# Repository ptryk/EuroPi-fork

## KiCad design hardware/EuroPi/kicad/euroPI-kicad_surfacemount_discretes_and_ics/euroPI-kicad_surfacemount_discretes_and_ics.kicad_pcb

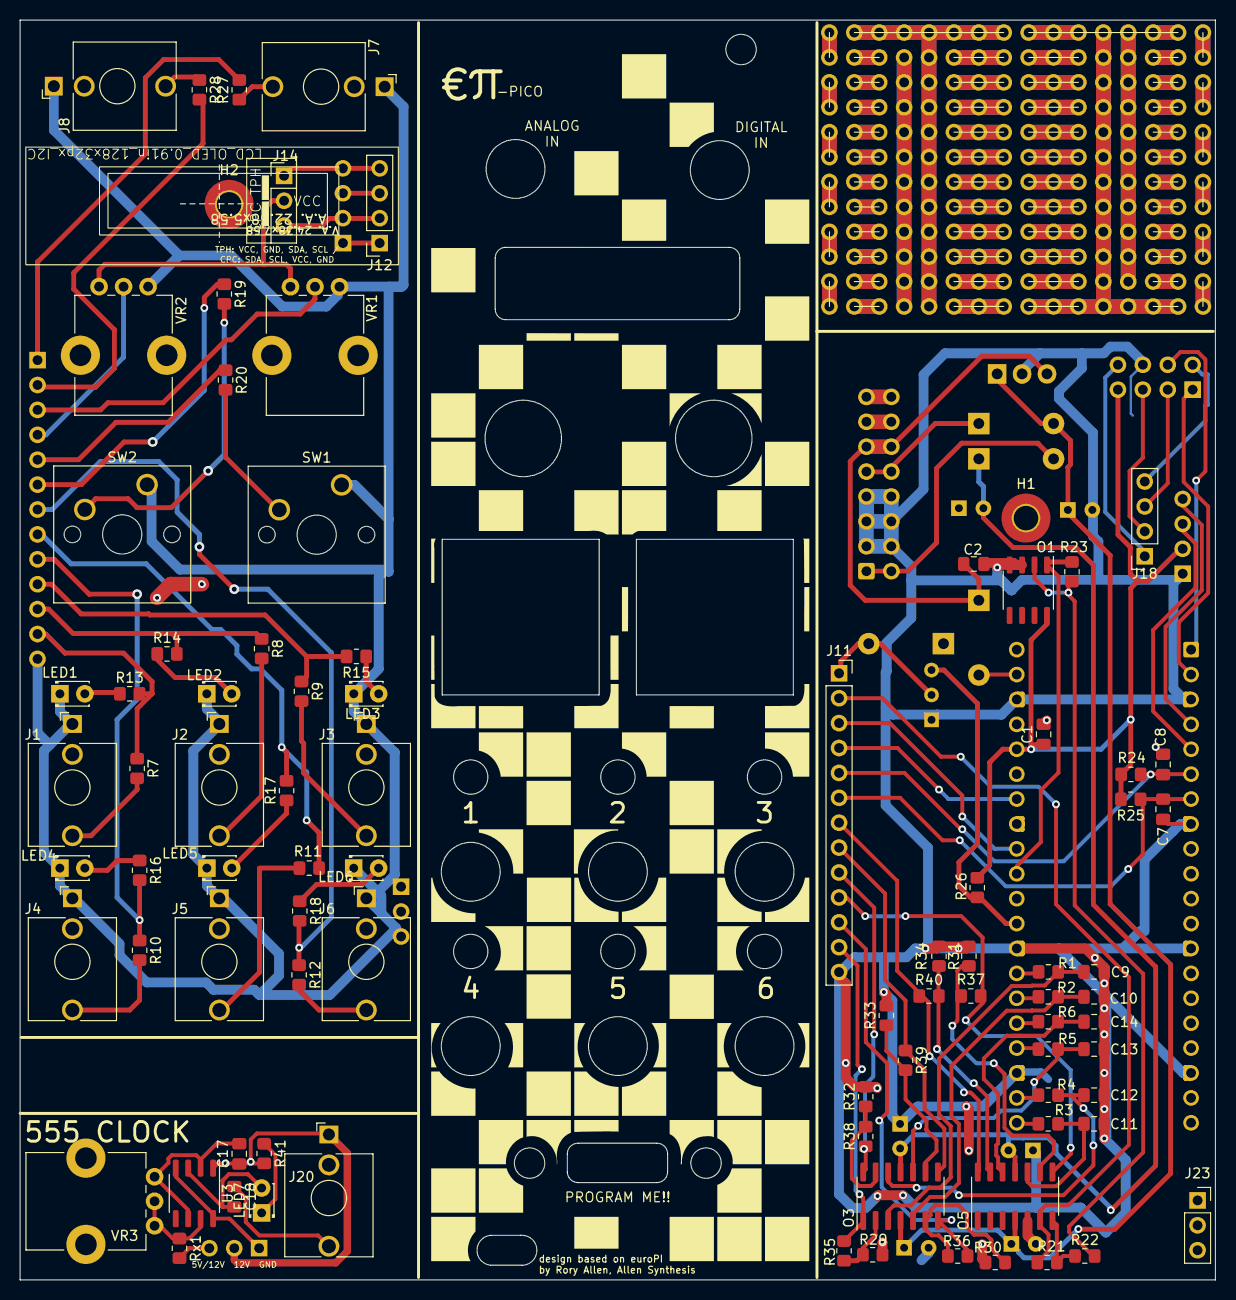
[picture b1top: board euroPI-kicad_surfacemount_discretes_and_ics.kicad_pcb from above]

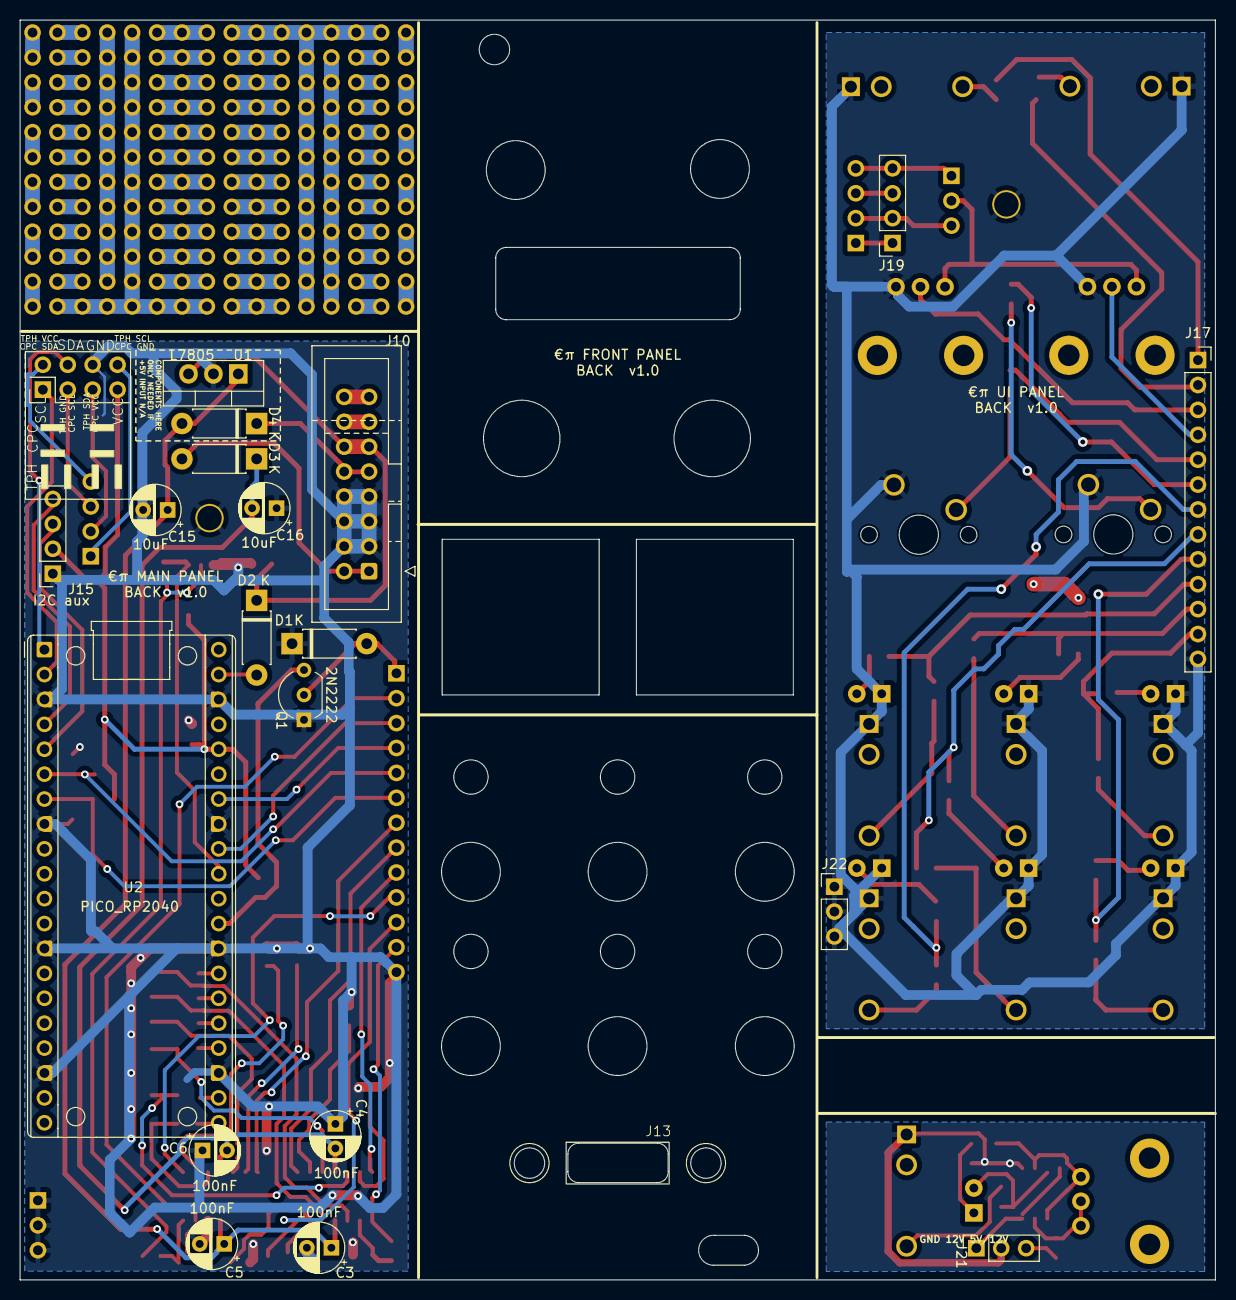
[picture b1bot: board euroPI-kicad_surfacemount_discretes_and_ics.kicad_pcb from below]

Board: 2 copper layers, 121.9 x 128.5 mm, 107 parts (21 on the bottom side), 73 nets.

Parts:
C1, C2, C17: 1uF; C_0805_2012Metric_Pad1.18x1.45mm_HandSolder
C3, C4, C5, C6: 100nF; CP_Radial_D5.0mm_P2.50mm
C7, C8, C9, C10, C11, C12, C13, C14: 100nF; C_0805_2012Metric_Pad1.18x1.45mm_HandSolder
C15, C16: 10uF; CP_Radial_D5.0mm_P2.50mm
C18: 10uF; C_0805_2012Metric_Pad1.18x1.45mm_HandSolder
D1, D2, D3, D4: 1N5817 Schottky Diode; D_DO-41_SOD81_P7.62mm_Horizontal
H1, H2: MountingHole_Pad; MountingHole_2.5mm_Pad_TopOnly
J1: Output 1 Jack; Jack_3.5mm_QingPu_WQP-PJ398SM_Vertical_CircularHoles
J2: Output 2 Jack; Jack_3.5mm_QingPu_WQP-PJ398SM_Vertical_CircularHoles
J3: Output 3 Jack; Jack_3.5mm_QingPu_WQP-PJ398SM_Vertical_CircularHoles
J4: Output 4 Jack; Jack_3.5mm_QingPu_WQP-PJ398SM_Vertical_CircularHoles
J5, J20: Output 5 Jack; Jack_3.5mm_QingPu_WQP-PJ398SM_Vertical_CircularHoles
J6: Output 6 Jack; Jack_3.5mm_QingPu_WQP-PJ398SM_Vertical_CircularHoles
J7: Digital Input Jack; Jack_3.5mm_QingPu_WQP-PJ398SM_Vertical_CircularHoles
J8: Analogue Input Jack; Jack_3.5mm_QingPu_WQP-PJ398SM_Vertical_CircularHoles
J10: Eurorack Power 2x8 16p; IDC-Header_euroRack-2x08_and_2x05_P2.54mm_Vertical
J11: Conn_01x13_Socket; PinSocket_1x13_P2.54mm_Vertical
J12: OLED 64x128; LCD_OLED_0.91in_128x32px_I2C
J13: USB_B_Micro; USBmicroB_panelMount
J14: Conn_01x03_Pin; OLED_switch_TPH-CPC_VCC+3v
J15: I2C aux; PinSocket_1x04_P2.54mm_Vertical
J16: Conn_02x04_Top_Bottom; OLED_switch_TPH-CPC
J17: Conn_01x13_Pin; PinSocket_1x13_P2.54mm_Vertical
J18: Conn_01x04_Pin; PinSocket_1x04_P2.54mm_Vertical
J19: Conn_01x04_Socket; PinSocket_1x04_P2.54mm_Vertical
J21: Conn_01x03_Pin; PinSocket_1x03_P2.54mm_Vertical
J22: Conn_01x03_Pin; PinHeader_1x03_P2.54mm_Vertical
J23: Conn_01x03_Socket; PinSocket_1x03_P2.54mm_Vertical
LED1, LED2, LED3, LED4, LED5, LED6, LED7: LED; LED_D1.8mm_W3.3mm_H2.4mm
O1: MCP6002; SO-8_3.9x4.9mm_P1.27mm
O3: TL074-1; SO-14_3.9x8.65mm_P1.27mm
O5: TL074-2; SO-14_3.9x8.65mm_P1.27mm
Q1: 2N2222; TO-92_Inline_Wide
R1, R2, R3, R4, R5, R6, R7, R8, R9, R10, R11, R12, R19, R20, R41: 1K; R_0805_2012Metric_Pad1.20x1.40mm_HandSolder
R13, R14, R15, R16, R17, R18: 4K7; R_0805_2012Metric_Pad1.20x1.40mm_HandSolder
R21, R22, R23: 22K; R_0805_2012Metric_Pad1.20x1.40mm_HandSolder
R24, R25, R26: 10K; R_0805_2012Metric_Pad1.20x1.40mm_HandSolder
R27, R28, R29, R30, R31, R32, R33, R34: 100K; R_0805_2012Metric_Pad1.20x1.40mm_HandSolder
R35, R36, R37, R38, R39, R40: 220K; R_0805_2012Metric_Pad1.20x1.40mm_HandSolder
Rx1: 1K; R_0805_2012Metric_Pad1.20x1.40mm_HandSolder
SW1, SW2: SW_Push; SW_Cherry_MX_1.00u_PCB
U1: L7805; TO-220-3_Vertical
U2: PICO_RP2040; RaspberryPi_Pico_Common_THT-minimal_courtyard_assumed_mount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
U3: LM555xN; SO-8_3.9x4.9mm_P1.27mm
VR1: KNOB 1; Potentiometer_Bourns_PTV09A-1_Single_Vertical
VR2: KNOB 2; Potentiometer_Bourns_PTV09A-1_Single_Vertical
VR3: 10K; Potentiometer_Bourns_PTV09A-1_Single_Vertical

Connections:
+5V: C2.1, D2.1 (A), J10.11, J10.12, J21.3, Rx1.2, U1.3 (OUT)
-12V: C4.2, C6.2, C16.2, D3.1 (A), O3.11 (V-), O5.11 (V-)
CJ1: J11.12, J17.12, O3.1, R7.1, R13.2, R35.1
CJ2: J11.11, J17.11, O3.7, R8.1, R14.2, R36.1
CJ3: J11.10, J17.10, O5.8, R9.1, R15.2, R37.1
CJ4: J11.9, J17.9, O3.14, R10.1, R16.2, R38.1
CJ5: J11.8, J17.8, O3.8, R11.1, R17.2, R39.1
CJ6: J11.7, J17.7, O5.14, R12.1, R18.2, R40.1
CJA: J11.2, J17.2, O5.6 (-), R21.1, R28.2
CJD: D1.2 (K), J11.1, J17.1, Q1.2 (B), R27.2
CK1: J11.3, J17.3, U2.32 (GP27), VR1.2
CK2: J11.4, J17.4, U2.34 (GP28), VR2.2
CS1: C8.1, J11.5, J17.5, R20.1, R24.1, U2.6 (GP4)
CS2: C7.1, J11.6, J17.6, R19.1, R25.1, U2.7 (GP5)
GP0: J16.6, U2.1 (GP0)
GP1: J16.1, U2.2 (GP1)
GP2: J15.4, U2.4 (GP2)
GP3: J15.3, U2.5 (GP3)
GP16: R3.2, U2.21 (GP16)
GP17: R4.2, U2.22 (GP17)
GP18: R5.2, U2.24 (GP18)
GP19: R6.2, U2.25 (GP19)
GP20: R2.2, U2.26 (GP20)
GP21: R1.2, U2.27 (GP21)
GP22: Q1.3 (C), R26.2, U2.29 (GP22)
GP26: O1.1, R23.2, U2.31 (GP26)
I2C_GND: C1.2, C2.2, C3.2, C4.1, C5.2, C6.1, C7.2, C8.2, C9.2, C10.2, C11.2, C12.2, C13.2, C14.2, C15.2, C16.1, C17.1, D1.1 (A), H1.1, H2.1, J1.S, J2.S, J3.S, J4.S, J5.S, J6.S, J7.S, J8.S, J10.3, J10.4, J10.5, J10.6, J10.7, J10.8, J11.13, J15.1, J16.7, J17.13, J20.S, J21.2, J22.1, J22.2, J22.3, J23.1, J23.2, J23.3, LED1.1 (K), LED2.1 (K), LED3.1 (K), LED4.1 (K), LED5.1 (K), LED6.1 (K), O1.3 (+), O1.4 (V-), O5.5 (+), Q1.1 (E), R29.2, R30.2, R31.2, R32.2, R33.2, R34.2, R41.2, SW1.1, SW2.1, U1.2 (GND), U2.3 (GND), U2.8 (GND), U2.13 (GND), U2.18 (GND), U2.23 (GND), U2.28 (GND), U2.33 (GND), U2.38 (GND), U3.1 (GND), VR1.3, VR2.3
I2C_VCC: C1.1, J14.2, J15.2, J16.4, O1.8 (V+), R24.2, R25.2, R26.1, U2.36 (3V3), VR1.1, VR2.1
unnamed: C18.1, J20.T
unnamed: D2.2 (K), U2.39 (VSYS)
unnamed: D3.2 (K), J10.1, J10.2
unnamed: D4.1 (A), J10.9, J10.10
unnamed: J1.T, R7.2
unnamed: J2.T, R8.2
unnamed: J3.T, R9.2
unnamed: J4.T, R10.2
unnamed: J5.T, R11.2
unnamed: J6.T, R12.2
unnamed: J7.T, R27.1
unnamed: J8.T, R28.1
unnamed: J10.13, J10.14
unnamed: J10.15, J10.16
unnamed: LED1.2 (A), R13.1
unnamed: LED2.2 (A), R14.1
unnamed: LED3.2 (A), R15.1
unnamed: LED4.2 (A), R16.1
unnamed: LED5.2 (A), R17.1
unnamed: LED6.2 (A), R18.1
unnamed: C18.2, LED7.2 (A), U3.3 (Q)
unnamed: LED7.1 (K), R41.1
unnamed: O1.2 (-), R22.2, R23.1
unnamed: C9.1, O3.3 (+), R1.1
unnamed: O3.2 (-), R29.1, R35.2
unnamed: C10.1, O3.5 (+), R2.1
unnamed: O3.6 (-), R30.1, R36.2
unnamed: C13.1, O3.10 (+), R5.1
unnamed: O3.9 (-), R33.1, R39.2
unnamed: C12.1, O3.12 (+), R4.1
unnamed: O3.13 (-), R32.1, R38.2
unnamed: O5.7, R21.2, R22.1
unnamed: C11.1, O5.10 (+), R3.1
unnamed: O5.9 (-), R31.1, R37.2
unnamed: C14.1, O5.12 (+), R6.1
unnamed: O5.13 (-), R34.1, R40.2
unnamed: R19.2, SW2.2
unnamed: R20.2, SW1.2
unnamed: Rx1.1, U3.7 (DIS), VR3.2, VR3.3
unnamed: C17.2, U3.2 (TR), U3.6 (THR), VR3.1
TPH GND / CPC SCL: J12.3, J16.2, J18.3, J19.3
TPH SCL / CPC GND: J12.1, J16.8, J18.1, J19.1
TPH SDA / CPC VCC: J12.2, J14.3, J16.3, J18.2, J19.2
TPH VCC / CPC SDA: J12.4, J14.1, J16.5, J18.4, J19.4
~: C3.1, C5.1, C15.1, D4.2 (K), J21.1, O3.4 (V+), O5.4 (V+), U1.1 (IN), U3.4 (R), U3.8 (VCC)

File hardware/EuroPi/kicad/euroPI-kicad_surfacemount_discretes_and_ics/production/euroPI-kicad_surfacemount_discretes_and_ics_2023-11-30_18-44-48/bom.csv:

Designator,Footprint,Quantity,Value,LCSC Part #
"C1, C17, C2",0805,3,1uF,
"C10, C11, C12, C13, C14, C3, C4, C5, C6, C7, C8, C9",0805,12,100nF,
"C15, C16, C18",0805,3,10uF,
"D1, D2, D3, D4",0805,4,"type=""D"" model=""DIODE"" lib=""""",
J1,Jack_3.5mm_QingPu_WQP-PJ398SM_Vertical_CircularHoles,1,Output 1 Jack,
J10,IDC-Header_euroRack-2x08_and_2x05_P2.54mm_Vertical,1,Eurorack Power 2x8 16p,
J11,PinSocket_1x13_P2.54mm_Vertical,1,Conn_01x13_Socket,
J12,LCD_OLED_0.91in_128x32px_I2C,1,OLED 64x128,
J13,USBmicroB_panelMount,1,USB_B_Micro,
J14,OLED_switch_TPH-CPC_VCC+3v,1,Conn_01x03_Pin,
"J15, J18",PinSocket_1x04_P2.54mm_Vertical,2,Conn_01x04_Pin,
J16,OLED_switch_TPH-CPC,1,Conn_02x04_Top_Bottom,
J17,PinSocket_1x13_P2.54mm_Vertical,1,Conn_01x13_Pin,
J19,PinSocket_1x04_P2.54mm_Vertical,1,Conn_01x04_Socket,
J2,Jack_3.5mm_QingPu_WQP-PJ398SM_Vertical_CircularHoles,1,Output 2 Jack,
"J20, J5",Jack_3.5mm_QingPu_WQP-PJ398SM_Vertical_CircularHoles,2,Output 5 Jack,
J21,PinSocket_1x03_P2.54mm_Vertical,1,Conn_01x03_Pin,
J3,Jack_3.5mm_QingPu_WQP-PJ398SM_Vertical_CircularHoles,1,Output 3 Jack,
J4,Jack_3.5mm_QingPu_WQP-PJ398SM_Vertical_CircularHoles,1,Output 4 Jack,
J6,Jack_3.5mm_QingPu_WQP-PJ398SM_Vertical_CircularHoles,1,Output 6 Jack,
J7,Jack_3.5mm_QingPu_WQP-PJ398SM_Vertical_CircularHoles,1,Digital Input Jack,
J8,Jack_3.5mm_QingPu_WQP-PJ398SM_Vertical_CircularHoles,1,Analogue Input Jack,
"LED1, LED2, LED3, LED4, LED5, LED6, LED7",LED_D1.8mm_W3.3mm_H2.4mm,7,LED,
O1,SO-8_3.9x4.9mm_P1.27mm,1,MCP6002,
O3,SO-14_3.9x8.65mm_P1.27mm,1,TL074-1,
O5,SO-14_3.9x8.65mm_P1.27mm,1,TL074-2,
Q1,SOT-23,1,2N2222,
"R1, R10, R11, R12, R19, R2, R20, R3, R4, R41, R5, R6, R7, R8, R9, Rx1",0805,16,1K,
"R13, R14, R15, R16, R17, R18",0805,6,4K7,
"R21, R22, R23",0805,3,22K,
"R24, R25, R26",0805,3,10K,
"R27, R28, R29, R30, R31, R32, R33, R34",0805,8,100K,
"R35, R36, R37, R38, R39, R40",0805,6,220K,
"SW1, SW2",SW_Cherry_MX_1.00u_PCB,2,SW_Push,
U1,TO-252-3_TabPin2,1,L7805,
U2,RaspberryPi_Pico_Common_THT-minimal_courtyard_assumed_mounted_high,1,PICO_RP2040,
U3,SO-8_3.9x4.9mm_P1.27mm,1,LM555xN,
VR1,Potentiometer_Bourns_PTV09A-1_Single_Vertical,1,KNOB 1,
VR2,Potentiometer_Bourns_PTV09A-1_Single_Vertical,1,KNOB 2,
VR3,Potentiometer_Bourns_PTV09A-1_Single_Vertical,1,10K,

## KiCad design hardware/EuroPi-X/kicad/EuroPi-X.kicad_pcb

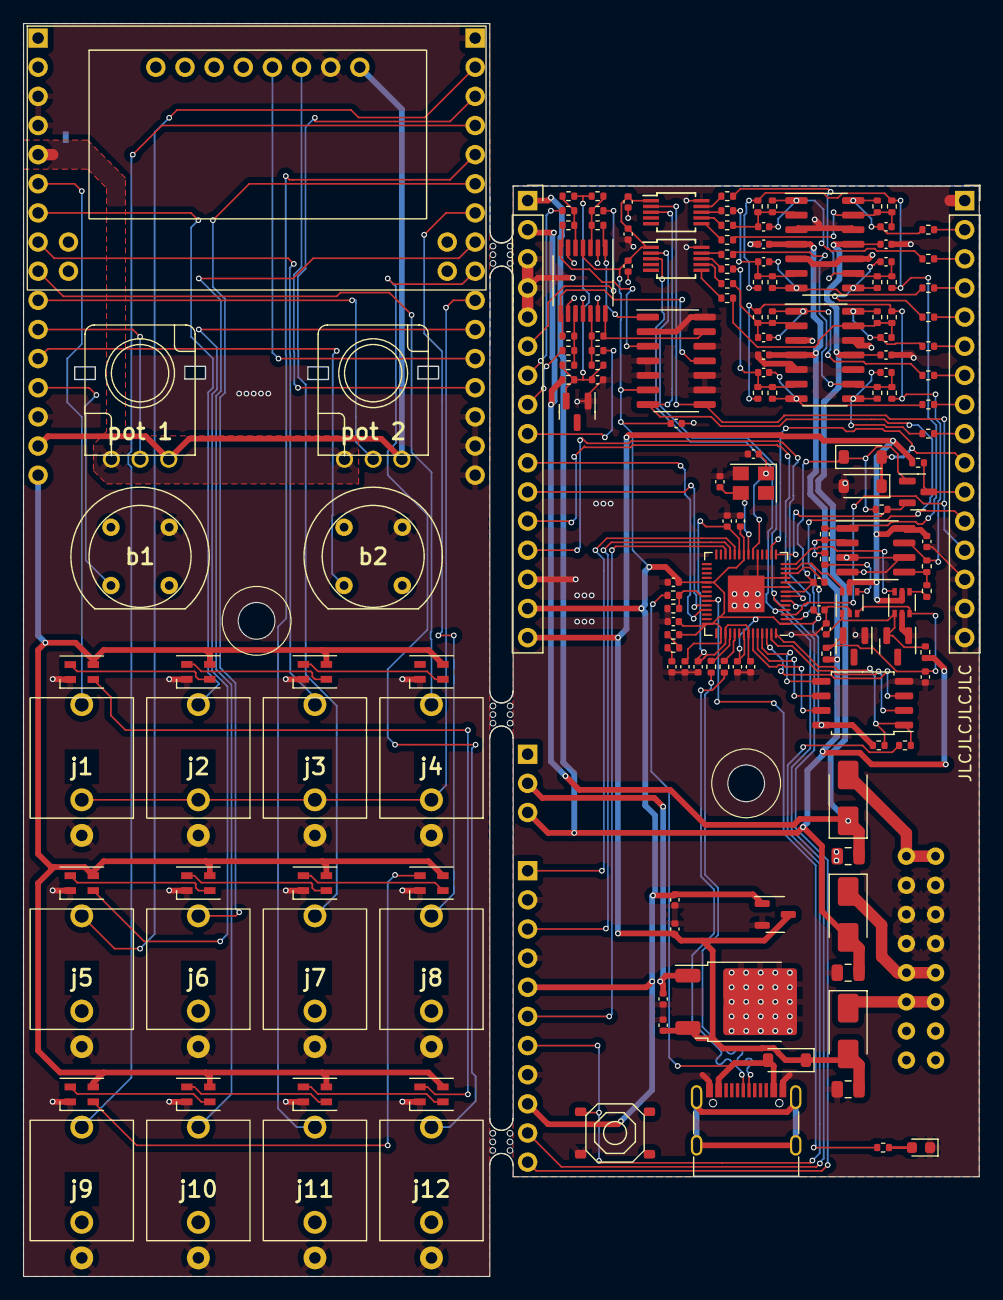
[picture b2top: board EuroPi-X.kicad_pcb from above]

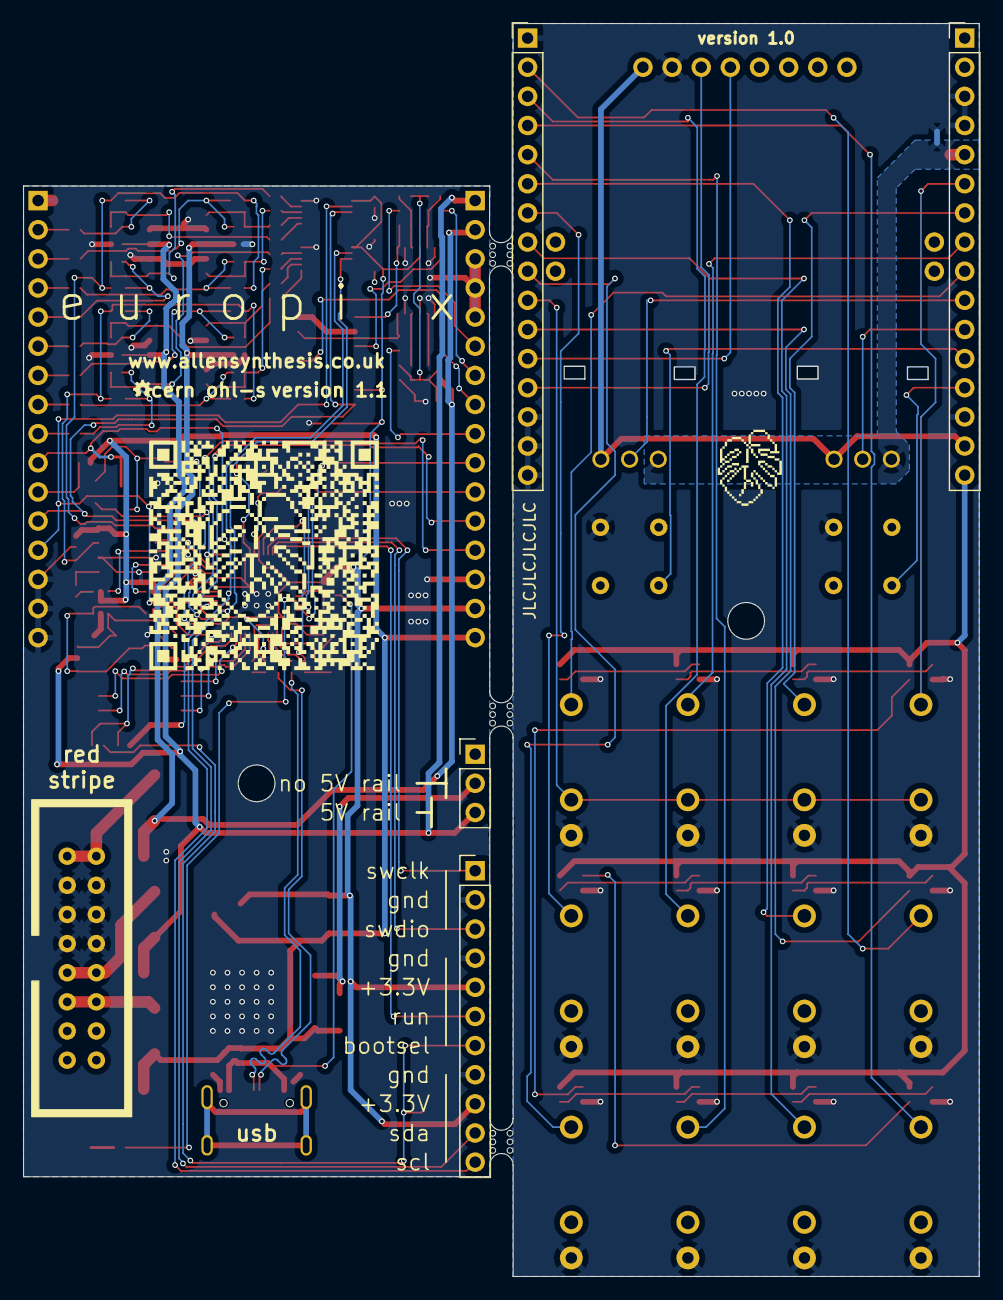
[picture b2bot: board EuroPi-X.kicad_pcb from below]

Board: 2 copper layers, 83.3 x 109.2 mm, 169 parts (6 on the bottom side), 133 nets.

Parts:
C1, C5, C6, C14, C16, C18, C21, C22, C23, C24, C27, C31, C35, C36, C37, C38, C39, C40, C41: 100n; C_0402_1005Metric
C2, C3, C4, C7, C10: 1u; C_0402_1005Metric
C8, C9: 10p; C_0402_1005Metric
C11, C12, C19, C20, C29, C30, C32, C33: 100p; C_0402_1005Metric
C13, C15, C17: 2u2; C_0402_1005Metric
C25, C26, C28: 10u; C_0805_2012Metric
D1, D2, D5: type="D" model="DIODE" lib=""; D_SMA
D3, D4, D6: D; D_SOD-123
D7: LED; LED_0603_1608Metric
DAC1, DAC2: MCP4728; MSOP-10_3x3mm_P0.5mm
J1, J2: Conn_01x16_Pin; PinHeader_1x16_P2.54mm_Vertical
J3, J4, J6, J7, J9, J10, J12, J13, J14, J15, J16, J17: Thonkiconn_Mono_Jack; Thonkiconn Mono Jack
J5, J8: Conn_01x16_Pin; PinSocket_1x16_P2.54mm_Vertical
J11: Conn_02x08_Odd_Even; Eurorack Power Header 16 Pin Unlabeled
J18: Conn_01x03_Pin; PinHeader_1x03_P2.54mm_Vertical
J22: Conn_01x11_Pin; PinHeader_1x11_P2.54mm_Vertical
LED1, LED2, LED3, LED4, LED5, LED6, LED7, LED8, LED9, LED10, LED11, LED12: SK6805; LED_SK6805_PLCC4_2.4x2.7mm_P1.3mm
NT1: NetTie_2; NetTie-2_SMD_Pad0.5mm
OLED1: Enoki OLED SSD1306 128x64
P1: USB_C_Plug_USB2.0; USB_C_Receptacle_G-Switch_GT-USB-7010ASV
P2, P3: Potentiometer_9mm_Vertical_Linear; Potentiometer 9mm Vertical Linear Centred
Q1: BSS138; SOT-23
R1, R2, R3: 2K2; R_0402_1005Metric
R4, R5: 27R4; R_0402_1005Metric
R6, R7, R10, R59: 10K; R_0402_1005Metric
R8, R9, R16, R17, R31, R32, R45, R46, R53, R54, R55, R61: 270K; R_0402_1005Metric
R11, R18, R19, R33, R34, R47, R48, R56, R57: 1K; R_0402_1005Metric
R12, R13, R14, R15, R20, R21, R22, R23, R27, R28, R29, R30, R35, R36, R37, R38, R41, R42, R43, R44, R49, R50, R51, R52: 100K; R_0402_1005Metric
R24: 1R; R_0402_1005Metric
R25, R26, R39, R40: 15K; R_0402_1005Metric
R58: 5K6; R_0402_1005Metric
R60, R62: 200R; R_0402_1005Metric
SW1: B1; Switch Tactile Momentary C&K
SW2: B2; Switch Tactile Momentary C&K
SW3: TS-1187A-B-A-B
SW4, SW5: SOT-363_SC-70-6
U1: MCP6002-xSN; SOIC-8_3.9x4.9mm_P1.27mm
U2: LM4040DBZ-2.0; SOT-23
U3: LM4040DBZ-10; SOT-23
U4: RP2040; QFN-56-1EP_7x7mm_P0.4mm_EP3.2x3.2mm
U5: SOT-23-3
U6: SOIC-8_5.23x5.23mm_P1.27mm
U7, U8: TL074; SOIC-14_3.9x8.7mm_P1.27mm
U9: MCP6004; TSSOP-14_4.4x5mm_P0.65mm
U10: MCP3428; SOIC-14_3.9x8.7mm_P1.27mm
U11: L7805; TO-252-2
U12: LM4040DBZ-4.1; SOT-23
Y1: Crystal_GND2; Crystal_SMD_3225-4Pin_3.2x2.5mm
mouse-bite-2mm-slot, mouse-bite-2mm-slot#2, mouse-bite-2mm-slot#3: VAL**; mouse-bite-2mm-slot

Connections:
+1V1: C13.1, C16.1, C41.1, U4.23 (DVDD), U4.45 (VREG_VOUT), U4.50 (DVDD)
+3.3V: C1.1, C5.1, C6.1, C10.1, C14.1, C15.1, C27.1, C31.1, C37.1, C38.1, C39.1, C40.1, D3.1 (K), DAC1.1 (VDD), DAC2.1 (VDD), J5.15, J22.5, J22.9, Q1.1 (G), R6.2, R10.1, R60.2, U4.1 (IOVDD), U4.8 (GPIO6), U4.10 (IOVDD), U4.22 (IOVDD), U4.33 (IOVDD), U4.42 (IOVDD), U4.44 (VREG_IN), U4.49 (IOVDD), U5.1 (OUT), U6.8 (VCC), U9.4 (V+), U10.6 (VDD)
+5V: C7.1, C18.1, C28.1, C36.1, D5.2 (K), D6.1 (K), J5.16, R7.2, SW4.5 (VCC), SW5.5 (VCC), U1.8 (V+), U5.3 (EN), U11.3 (OUT)
+12V: C21.1, C23.1, C25.1, D1.2 (K), J5.1, J18.3, R1.2, R2.2, U7.4 (V+), U8.4 (V+)
-12V: C22.2, C24.2, C26.2, D2.1 (A), J5.2, R3.2, U7.11 (V-), U8.11 (V-)
/5VREG_INPUT: C35.1, J18.2, U11.1 (IN)
/+2.048VREF: C3.1, R2.1, SW4.1 (B1), SW5.1 (B1), U2.2 (A)
/+3.3V_FRONT: J1.15, OLED1.8 (3V3), P2.3, P3.3
/+4.096VREF: C2.1, R1.1, SW4.3 (B0), SW5.3 (B0), U12.2 (A)
/+5V_EURO: D5.1 (A), J11.11, J11.12
/+5V_FRONT: J1.16, LED1.4 (VDD), LED2.4 (VDD), LED3.4 (VDD), LED4.4 (VDD), LED5.4 (VDD), LED6.4 (VDD), LED7.4 (VDD), LED8.4 (VDD), LED9.4 (VDD), LED10.4 (VDD), LED11.4 (VDD), LED12.4 (VDD)
/-10VREF: C4.1, R3.1, R20.1, R22.1, R35.1, R37.1, U3.2 (A)
/ADC_ADVDD: C17.1, R24.1
/ADC_INPUT_1: R25.2, U9.1, U10.1 (CH1+)
/ADC_INPUT_2: R40.2, U9.7, U10.3 (CH2+)
/ADC_INPUT_3: R26.2, U9.8, U10.11 (CH3+)
/ADC_INPUT_4: R39.2, U9.14, U10.13 (CH4+)
/ADC_VREF: R24.2, R60.1
/AGND_FRONT: J1.5, NT1.1, P2.1, P3.1
/BOOTSEL: J22.7, R11.2, SW3.1 (A)
/BUTTON_1: J5.13, U4.6 (GPIO4)
/BUTTON_1_FRONT: J1.13, SW1.1
/BUTTON_2: J5.12, U4.7 (GPIO5)
/BUTTON_2_FRONT: J1.12, SW2.1
/CV_INPUT_1: J5.6, R21.1
/CV_INPUT_1_FRONT: J1.6, J3.3 (T)
/CV_INPUT_2: J5.7, R38.1
/CV_INPUT_2_FRONT: J1.7, J10.3 (T)
/CV_INPUT_3: J5.8, R23.1
/CV_INPUT_3_FRONT: J1.8, J4.3 (T)
/CV_INPUT_4: J5.9, R36.1
/CV_INPUT_4_FRONT: J1.9, J9.3 (T)
/CV_OUTPUT_1: J8.2, R18.1
/CV_OUTPUT_1_FRONT: J2.2, J6.3 (T)
/CV_OUTPUT_2: J8.3, R33.1
/CV_OUTPUT_2_FRONT: J2.3, J12.3 (T)
/CV_OUTPUT_3: J8.4, R47.1
/CV_OUTPUT_3_FRONT: J2.4, J14.3 (T)
/CV_OUTPUT_4: J8.5, R56.1
/CV_OUTPUT_4_FRONT: J2.5, J16.3 (T)
/CV_OUTPUT_5: J8.6, R19.1
/CV_OUTPUT_5_FRONT: J2.6, J7.3 (T)
/CV_OUTPUT_6: J8.7, R34.1
/CV_OUTPUT_6_FRONT: J2.7, J13.3 (T)
/CV_OUTPUT_7: J8.8, R48.1
/CV_OUTPUT_7_FRONT: J2.8, J15.3 (T)
/CV_OUTPUT_8: J8.9, R57.1
/CV_OUTPUT_8_FRONT: J2.9, J17.3 (T)
/DAC_1_OFFSET: R9.1, R12.2, R27.2, R41.2, R49.2, U1.1
/DAC_1_OFFSET_INVERTED: R8.2, SW4.4 (A)
/DAC_1_OUTA: DAC1.6 (VOUTA), R13.2
/DAC_1_OUTB: DAC1.7 (VOUTB), R28.2
/DAC_1_OUTC: DAC1.8 (VOUTC), R42.2
/DAC_1_OUTD: DAC1.9 (VOUTD), R50.2
/DAC_1_OUTPUT_MODE: SW4.6 (SEL), U4.13 (GPIO10)
/DAC_2_OFFSET: R14.2, R29.2, R43.2, R51.2, R61.1, U1.7
/DAC_2_OFFSET_INVERTED: R55.2, SW5.4 (A)
/DAC_2_OUTA: DAC2.6 (VOUTA), R15.2
/DAC_2_OUTB: DAC2.7 (VOUTB), R30.2
/DAC_2_OUTC: DAC2.8 (VOUTC), R44.2
/DAC_2_OUTD: DAC2.9 (VOUTD), R52.2
/DAC_2_OUTPUT_MODE: SW5.6 (SEL), U4.14 (GPIO11)
/GND_FRONT: J1.3, J1.4, J1.14, J2.1, J2.14, J2.15, J2.16, J3.1 (E), J4.1 (E), J6.1 (E), J7.1 (E), J9.1 (E), J10.1 (E), J12.1 (E), J13.1 (E), J14.1 (E), J15.1 (E), J16.1 (E), J17.1 (E), LED1.2 (VSS), LED2.2 (VSS), LED3.2 (VSS), LED4.2 (VSS), LED5.2 (VSS), LED6.2 (VSS), LED7.2 (VSS), LED8.2 (VSS), LED9.2 (VSS), LED10.2 (VSS), LED11.2 (VSS), LED12.2 (VSS), NT1.2, OLED1.7 (GND), SW1.2, SW2.2
/GPIO_25_LED: R62.1, U4.37 (GPIO25)
/I2C0_SCL: DAC1.2 (SCL), J8.13, U4.3 (GPIO1), U10.8 (SCL)
/I2C0_SCL_FRONT: J2.13, OLED1.6 (SCK)
/I2C0_SDA: DAC1.3 (SDA), J8.12, U4.2 (GPIO0), U10.7 (SDA)
/I2C0_SDA_FRONT: J2.12, OLED1.5 (SDA)
/I2C1_SCL: DAC2.2 (SCL), J22.11, U4.5 (GPIO3)
/I2C1_SDA: DAC2.3 (SDA), J22.10, U4.4 (GPIO2)
/INPUT_DETECT: D3.2 (A), D4.1 (K), J8.10, U4.16 (GPIO13)
/INPUT_DETECT_FRONT: J2.10, J3.2 (TN), J4.2 (TN), J9.2 (TN), J10.2 (TN)
/KNOB_1: J5.11, U4.38 (GPIO26_ADC0)
/KNOB_1_FRONT: J1.11, P2.2
/KNOB_2: J5.10, U4.39 (GPIO27_ADC1)
/KNOB_2_FRONT: J1.10, P3.2
/NEOPIXEL_DATA_3V3: Q1.2 (S), R6.1, U4.15 (GPIO12)
/NEOPIXEL_DATA_5V: J8.11, Q1.3 (D), R7.1
/NEOPIXEL_DATA_FRONT: J2.11, LED1.3 (DIN)
/QSPI_CS: R10.2, R11.1, U4.56 (QSPI_SS), U6.1 (~CS)
/QSPI_SCLK: U4.52 (QSPI_SCLK), U6.6 (CLK)
/QSPI_SD0: U4.53 (QSPI_SD0), U6.5 (DI(IO0))
/QSPI_SD1: U4.55 (QSPI_SD1), U6.2 (DO(IO1))
/QSPI_SD2: U4.54 (QSPI_SD2), U6.3 (IO2)
/QSPI_SD3: U4.51 (QSPI_SD3), U6.7 (IO3)
/RUN: J22.6, U4.26 (RUN)
/SWCLK: J22.1, U4.24 (SWCLK)
/SWDIO: J22.3, U4.25 (SWD)
/USB_DETECT: R58.1, R59.2, U4.36 (GPIO24)
/USB_DN: P1.A7 (D-), R5.1
/USB_DP: P1.A6 (D+), R4.1
/VBUS: D6.2 (A), P1.A4 (VBUS), P1.A9 (VBUS), P1.B4 (VBUS), P1.B9 (VBUS), R58.2
/XTAL_IN: C8.2, U4.20 (XIN), Y1.1
/XTAL_OUT: C9.2, U4.21 (XOUT), Y1.3
Earth: C1.2, C2.2, C3.2, C4.2, C5.2, C6.2, C7.2, C8.1, C9.1, C10.2, C13.2, C14.2, C15.2, C16.2, C17.2, C18.2, C21.2, C22.1, C23.2, C24.1, C25.2, C26.1, C27.2, C28.2, C31.2, C35.2, C36.2, C37.2, C38.2, C39.2, C40.2, C41.2, D4.2 (A), D7.1 (K), DAC1.10 (VSS), DAC2.10 (VSS), J5.3, J5.4, J5.5, J5.14, J8.1, J8.14, J8.15, J8.16, J11.3, J11.4, J11.5, J11.6, J11.7, J11.8, J22.2, J22.4, J22.8, P1.A1 (GND), P1.A12 (GND), P1.B1 (GND), P1.B12 (GND), R59.1, SW3.3 (C), SW4.2 (GND), SW5.2 (GND), U1.3 (+), U1.4 (V-), U1.6 (-), U2.1 (K), U3.1 (K), U4.9 (GPIO7), U4.11 (GPIO8), U4.12 (GPIO9), U4.19 (TESTEN), U4.57 (GND), U5.2 (GND), U6.4 (GND), U7.3 (+), U7.5 (+), U7.10 (+), U7.12 (+), U8.3 (+), U8.5 (+), U8.10 (+), U8.12 (+), U9.2 (-), U9.6 (-), U9.9 (-), U9.11 (V-), U9.13 (-), U10.2 (CH1-), U10.4 (CH2-), U10.5 (VSS), U10.9 (Adr0), U10.10 (Adr1), U10.12 (CH3-), U10.14 (CH4-), U11.2 (GND), U12.1 (K), Y1.2
unnamed: C11.2, R16.1, R18.2, U7.14
unnamed: C12.2, R17.1, R19.2, U8.14
unnamed: C19.2, R31.1, R33.2, U7.1
unnamed: C20.2, R32.1, R34.2, U8.1
unnamed: C29.2, R45.1, R47.2, U7.7
unnamed: C30.2, R46.1, R48.2, U8.7
unnamed: C32.2, R53.1, R56.2, U7.8
unnamed: C33.2, R54.1, R57.2, U8.8
unnamed: D1.1 (A), J11.9, J11.10
unnamed: D2.2 (K), J11.1, J11.2
unnamed: D7.2 (A), R62.2
unnamed: LED1.1 (DOUT), LED3.3 (DIN)
unnamed: LED2.3 (DIN), LED7.1 (DOUT)
unnamed: LED2.1 (DOUT), LED4.3 (DIN)
unnamed: LED3.1 (DOUT), LED5.3 (DIN)
unnamed: LED4.1 (DOUT), LED6.3 (DIN)
unnamed: LED5.1 (DOUT), LED7.3 (DIN)
unnamed: LED6.1 (DOUT), LED8.3 (DIN)
unnamed: LED8.1 (DOUT), LED9.3 (DIN)
unnamed: LED10.3 (DIN), LED11.1 (DOUT)
unnamed: LED10.1 (DOUT), LED12.3 (DIN)
unnamed: LED9.1 (DOUT), LED11.3 (DIN)
unnamed: R8.1, R9.2, U1.2 (-)
unnamed: R55.1, R61.2, U1.5 (+)
unnamed: R5.2, U4.46 (USB_DM)
unnamed: R4.2, U4.47 (USB_DP)
unnamed: C19.1, R27.1, R28.1, R31.2, U7.2 (-)
unnamed: C29.1, R41.1, R42.1, R45.2, U7.6 (-)
unnamed: C32.1, R49.1, R50.1, R53.2, U7.9 (-)
unnamed: C11.1, R12.1, R13.1, R16.2, U7.13 (-)
unnamed: C20.1, R29.1, R30.1, R32.2, U8.2 (-)
unnamed: C30.1, R43.1, R44.1, R46.2, U8.6 (-)
unnamed: C33.1, R51.1, R52.1, R54.2, U8.9 (-)
unnamed: C12.1, R14.1, R15.1, R17.2, U8.13 (-)
unnamed: R20.2, R21.2, R25.1, U9.3 (+)
unnamed: R37.2, R38.2, R40.1, U9.5 (+)
unnamed: R22.2, R23.2, R26.1, U9.10 (+)
unnamed: R35.2, R36.2, R39.1, U9.12 (+)

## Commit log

2023-11-25 added mouse bites and combined the pcbs in kicad to allow producing them together used the mouse bites from miniOSC from benjiaomodular
2023-11-28 kicad version of pcb 40.64mm wide needs to fix schematic wiht oled cpc and tph should be additional connector or i2c
2023-11-28 cleaning pcb fixing connector i2c
2023-11-28 fixed eurorack connector to correct pin1 imported graphics
2023-11-28 minor fix to rear silkscreen for scoring
2023-11-28 further cleaning rearranging boards to make it easier to score for seperation
2023-11-28 cosmetics fixes and trardrops
2023-11-30 euroPI kicad version now including SMDs
2023-11-30 kicad smd :)
2023-11-30 THT version updated with ground plane
2023-11-30 euroPI base minor fixes incl adding ground plane
2023-12-01 small fixes
2023-12-02 wip tried a reroute should move power rail caps closer i think
2023-12-02 reorg continued mainly trying to get power filtering better situated
2023-12-02 updated with caps under sockets in order to improve power filtering as intended
2023-12-03 extra standoff :)
2023-12-03 incl standoffs to GND removed GND pin on headers
2023-12-07 small fixes added missed net and text around eurorack conn
2024-01-06 misc improvements THT fixed grounds and misc clean up issue likely still wtih usb output SMT redid caps to be near to necessary fixed GND and misc things to make it easier to hand solder
2024-01-09 smt updated and improved, gerbers updated and zipped todo fix proto board errors todo fix nets between boards
2024-01-17 some updates of smt version incl correcting layout component choices support structures

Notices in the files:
hardware/EuroPi-X/kicad/EuroPi-X.kicad_pcb:
cern ohl-s
